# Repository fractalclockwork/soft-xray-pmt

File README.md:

# soft-xray-pmt — Soft X-ray PMT (XP3312/SQ), stage 1

This repo is the **first stage** of a soft X-ray detector: power and sense bring-up for a surplus Photonis **XP3312/SQ** (SN 294056) on a wooden harness with its stock Philips medical I/O filter board (dual-row header + coax + local R/C). The board is a **filter/breakout**, not a full dynode divider — the Type A HV string and anode path are designed here before later detector integration. **No HV applied yet.**

*Bring-up harness: tube cradled on plywood, stock circular filter PCB, divider protoboard, banana HV + BNC anode.*

*Photocathode end of the tube in the harness cradles.*

## Prior — verified pin map (continuity 2026-11-01)

Unpowered DMM checks locked the tube↔header map and corrected the filter cluster. **PASS.** This is the prior gate for HV bring-up — not an energize stage.

| Item | Path |
|---|---|
| **Verified netlist** | [`docs/probable-netlist.md`](docs/probable-netlist.md) |
| Pin reconciliation | [`docs/pin-reconciliation.md`](docs/pin-reconciliation.md) |
| Continuity checklist | [`docs/continuity-checklist.md`](docs/continuity-checklist.md) |
| KiCad project | [`hardware/pmt-interface/`](hardware/pmt-interface/) |
| Schematic (page 1 filter) | [`hardware/pmt-interface/pmt-interface.kicad_sch`](hardware/pmt-interface/pmt-interface.kicad_sch) |
| Schematic (page 2 bringup) | [`hardware/pmt-interface/bringup-supply.kicad_sch`](hardware/pmt-interface/bringup-supply.kicad_sch) |
| Filter PCB (2-layer analogue) | [`hardware/pmt-interface/pmt-interface.kicad_pcb`](hardware/pmt-interface/pmt-interface.kicad_pcb) |
| Bring-up supply PCB | [`hardware/pmt-interface/bringup-supply.kicad_pcb`](hardware/pmt-interface/bringup-supply.kicad_pcb) |
| Filter PCB preview | [`docs/pmt-interface-pcb.pdf`](docs/pmt-interface-pcb.pdf) |
| Circular pin map | [`docs/tube-pin-map.md`](docs/tube-pin-map.md) |
| PDF preview | [`docs/pmt-interface-draft.pdf`](docs/pmt-interface-draft.pdf) |
| Photo BOM / traces | [`docs/photo-bom.md`](docs/photo-bom.md), [`docs/photo-trace-map.md`](docs/photo-trace-map.md) |
| Datasheets | [`docs/sources.md`](docs/sources.md), [`docs/datasheets/`](docs/datasheets/) |
| Board photos | [`docs/img/`](docs/img/) |
| Bring-up harness photos | [`docs/img/bringup/`](docs/img/bringup/) |

## HV bring-up (multi-stage)

Gated ladder: design/build divider + anode measure **before** any HV; dark ramp with encoded voltage ceilings; scope anode before Pico. **No HV applied yet.**

| Item | Path |
|---|---|
| **Bring-up index + status** | [`docs/bringup/README.md`](docs/bringup/README.md) |
| Voltage / current ceilings | [`docs/bringup/ceilings.md`](docs/bringup/ceilings.md) |
| **Bring-up BOM** (divider + anode + DNP) | [`docs/bringup/bom-divider.md`](docs/bringup/bom-divider.md) |
| Gate 0 design | [`docs/bringup/gate-0-design.md`](docs/bringup/gate-0-design.md) (**PASS**) |
| Gate 0b sch verify | [`docs/bringup/gate-0-sch-verify.md`](docs/bringup/gate-0-sch-verify.md) (**PASS**) |
| Gate 0c SPICE | [`docs/bringup/gate-0-spice.md`](docs/bringup/gate-0-spice.md) — KiCad (**PASS**) |
| Gate PCB bringup-supply | [`docs/bringup/gate-pcb-bringup.md`](docs/bringup/gate-pcb-bringup.md) (**PASS** 2026-11-02) |
| Next | Gate A stuff per [`bom-divider.md`](docs/bringup/bom-divider.md) → B → C → Stages 1–8 |

Ceilings (first pass): Stage 1 **100 V** → Stage 2 **400 V** → Stage 3 **800 V** → Stage 4 **1000 V** dark; abs max **1500 V**.

Gated sch→PCB: skill `kicad-gated-sch-pcb`; instance [`docs/bringup/design-process.md`](docs/bringup/design-process.md), commands [`hardware/pmt-interface/AGENTS.md`](hardware/pmt-interface/AGENTS.md).  
Schematic routing: [`.cursor/skills/kicad-schematic-routing/SKILL.md`](.cursor/skills/kicad-schematic-routing/SKILL.md).

```bash
python3 hardware/pmt-interface/gen_bringup_sch.py --validate   # tracked sch; no overwrite
python3 hardware/pmt-interface/gen_fp.py
python3 hardware/pmt-interface/gen_sch.py --validate          # page 1; does not rewrite bringup sch
python3 hardware/pmt-interface/gen_pcb.py                     # filter analogue (outside Gate PCB)
```

## Tube identity

- Photonis XP3312/SQ — Made in France
- Date 29-Sep-04, batch 04229, SN 294056
- PH 36 pC, PHR 8.7%

## Verified board map (summary)

Tube view: **bottom looking up**, `sp` south, pins **1…19 clockwise**.

J1 is a **DIP-14–style wide IC socket** (7.62 mm / 300 mil row spacing, wrap numbering — **not** IDC ribbon Odd/Even):

```text
  1 -------- 14
  2 -------- 13
  ...
  7 --------  8
```

| Electrode | Tube | Board |
|---|---|---|
| D1…D8 | 1,3,4,7,8,9,10,11 | J1 **8,9,6,5,4,12,3,2** |
| K | 16 | C1 `472Z` 2 kV to GND; R1 `1001` 1 kΩ → **J1.7** |
| A | 12 | coax center; R2 `115` ~1.1 MΩ → GND |
| GND | — | **J1.14** + coax shell |
| Filter | — | **D8** and **J1.13** each via tan MLCC to mid → R3 `100` 10 Ω → GND |

J1.1 / 10 / 11: photo-consistent NC (pads, no fan-out); DMM still required (11 least clear).

## License

SPDX-License-Identifier: `CERN-OHL-S-2.0`

Hardware sources and accompanying project materials are under the [CERN Open Hardware Licence Version 2 - Strongly Reciprocal](LICENSE). See also [`NOTICE`](NOTICE).

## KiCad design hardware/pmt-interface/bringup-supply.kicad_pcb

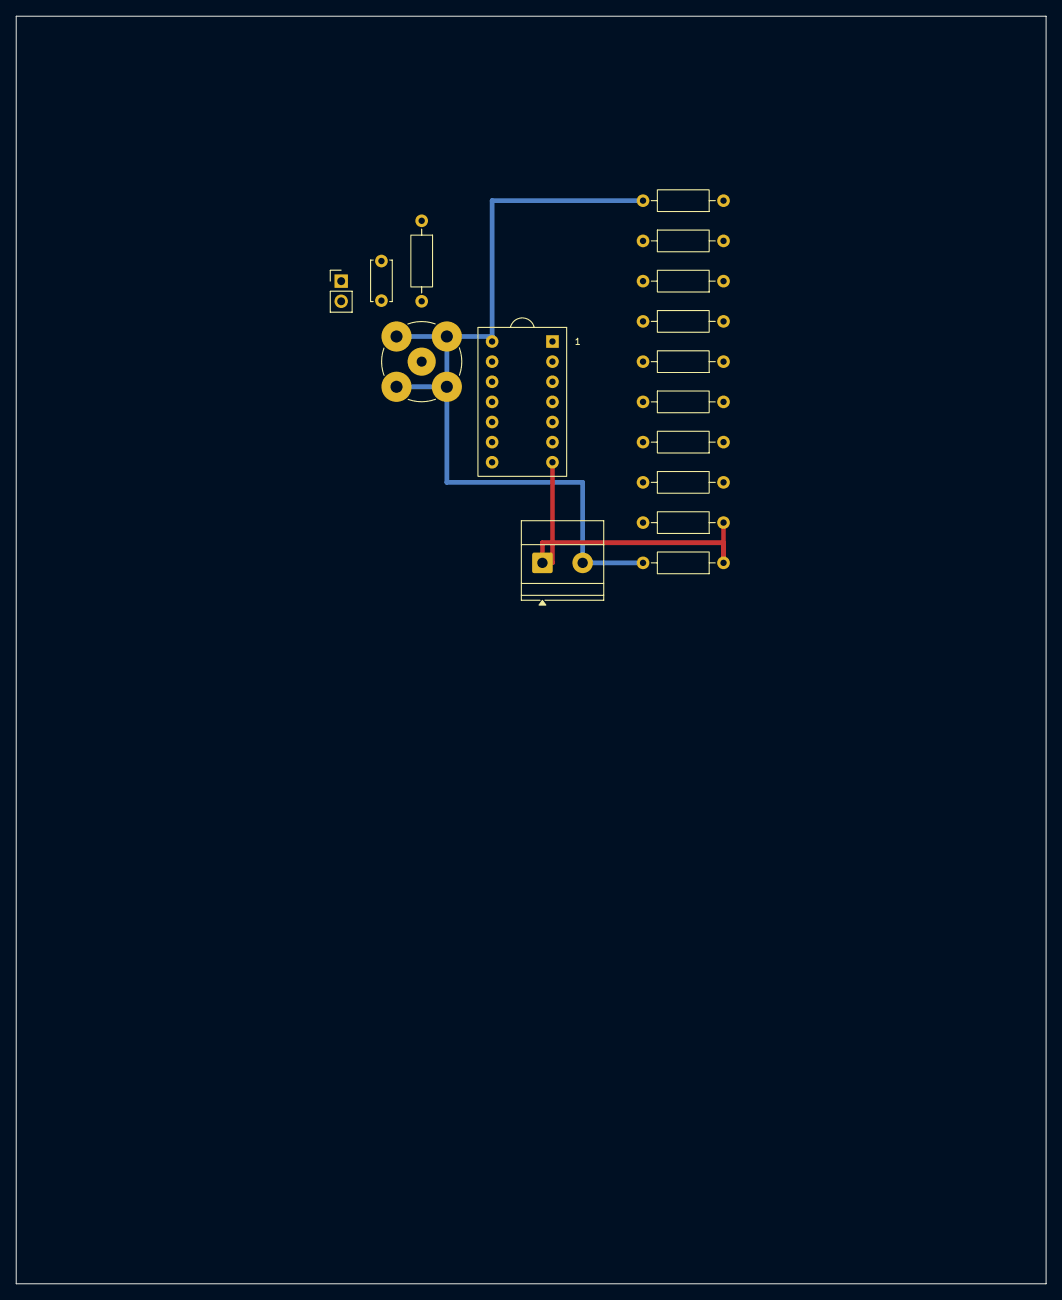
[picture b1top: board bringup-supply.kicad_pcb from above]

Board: 10 copper layers, 130.0 x 160.0 mm, 16 parts (0 on the bottom side), 12 nets.

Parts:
C4: 1nF; C_Disc_D5.0mm_W2.5mm_P5.00mm
J3: HV_IN; TerminalBlock_Phoenix_MKDS-1,5-2-5.08_1x02_P5.08mm_Horizont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
J4: MATE_J1; HDR_2x7_IC_Socket
J5: BNC_SCOPE; BNC_TEConnectivity_1478204_Vertical
JMP_DC: DC_COUPLE; PinHeader_1x02_P2.54mm_Vertical
R10: 4.4M; R_Axial_DIN0207_L6.3mm_D2.5mm_P10.16mm_Horizontal
R11, R12, R13: 3.3M; R_Axial_DIN0207_L6.3mm_D2.5mm_P10.16mm_Horizontal
R14, R15, R16, R17: 2.2M; R_Axial_DIN0207_L6.3mm_D2.5mm_P10.16mm_Horizontal
R18: 1.1M; R_Axial_DIN0207_L6.3mm_D2.5mm_P10.16mm_Horizontal
R19: 47R; R_Axial_DIN0207_L6.3mm_D2.5mm_P10.16mm_Horizontal
Rbleed: 22M; R_Axial_DIN0207_L6.3mm_D2.5mm_P10.16mm_Horizontal

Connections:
A: C4.1, JMP_DC.1, R19.1
D1: J4.8, R10.2, R11.1
D2: J4.9, R11.2, R12.1
D3: J4.6, R12.2, R13.1
D4: J4.5, R13.2, R14.1
D5: J4.4, R14.2, R15.1
D6: J4.12, R15.2, R16.1
D7: J4.3, R16.2, R17.1
D8: J4.2, R17.2, R18.1
GND: J3.2, J4.14, J5.2, R18.2, Rbleed.2
K: J3.1, J4.7, R10.1, Rbleed.1
SCOPE: C4.2, J5.1, JMP_DC.2, R19.2

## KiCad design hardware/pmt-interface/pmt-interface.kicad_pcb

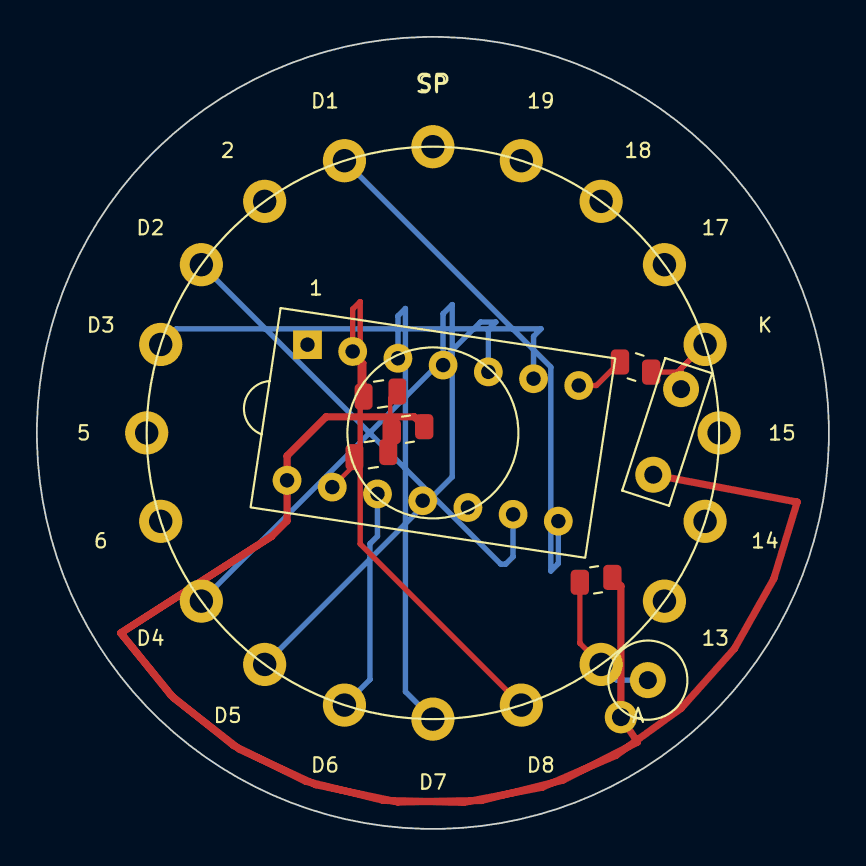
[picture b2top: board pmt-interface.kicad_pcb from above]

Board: 2 copper layers, 44.0 x 44.0 mm, 9 parts (1 on the bottom side), 14 nets.

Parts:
C1: 4.7nF 2kV; C_Disc_D7.5mm_W2.5mm_P5.00mm
C2: MLCC J1.13; C_0805_2012Metric
C3: MLCC D8; C_0805_2012Metric
J1: HDR_2x7_IC_Socket
J2: COAX; COAX_Edge
R1: 1k; R_0805_2012Metric
R2: 1.1M; R_0805_2012Metric
R3: 10R; R_0805_2012Metric
U1: XP3312/SQ; XP3312_FlyingLead

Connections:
A: J2.1, R2.1, U1.12
BYPASS_MID: C2.2, C3.2, R3.1
D1: J1.8, U1.1
D2: J1.9, U1.3
D3: J1.6, U1.4
D4: J1.5, U1.7
D5: J1.4, U1.8
D6: J1.12, U1.9
D7: J1.3, U1.10
D8: C3.1, J1.2, U1.11
GND: C1.2, J1.14, J2.2, R2.2, R3.2
J1.13: C2.1, J1.13
K: C1.1, R1.1, U1.16
R1_J1: J1.7, R1.2

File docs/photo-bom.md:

# Photo BOM — stock XP3312/SQ I/O filter board

Confidence: `FROM_PHOTO` unless noted. Values preferred over pencil notes when they conflict.

## Tube

| Field | Value | Source |
|---|---|---|
| Maker | PHOTONIS imaging sensors | IMG_6985 / 6998 |
| Type | XP3312/SQ | label |
| Date | 29-Sep-04 | label |
| Batch | 04229 | label |
| SN | 294056 | label |
| PH | 36 pC | label |
| PHR | 8.7% | label |
| Origin | Made in France | label |
| Side code | 331117031963 | label |

## Passive components on filter PCB

| Ref (draft) | Marking | Interpreted value | Role (hypothesis) | Photos |
|---|---|---|---|---|
| R1 / R_K | `1001` | **1 kΩ** | Cathode path series to header pin 7 | 6989, 7006 |
| R2 / R_A | `115` | **1.1 MΩ** | Anode load to GND (notes said 1 M) | 7005 |
| R3 / R_F | `100` | **10 Ω** | Mid-node → GND (between two filter MLCCs) | 7005 |
| C1 / C_HV | `472Z` `2KV` | **4.7 nF, Z tol, 2 kV** | Cathode bypass to GND | **7006** |
| C2 / C_F1 | unmarked tan MLCC | TBD (measure / mark) | **J1.13** ↔ filter mid (continuity) | 6993, 7005 |
| C3 / C_F2 | unmarked tan MLCC | TBD | **D8** ↔ filter mid (continuity) | 6993, 7005 |

## Connectors

| Ref | Description | Notes |
|---|---|---|
| J1 | **Wide IC / DIP-14 style socket** (≈7.62 mm row spacing, two rows of 7) | **Wrap numbering** (1–7 \| 14–8) like Prutchi XP2422 Fig. 3 / DIP-14; **not** IDC ribbon Odd/Even or 2.54 mm dual-row header body |
| J2 | Gold coax (SMA/SMB-style) | Center = anode signal; shell = GND |

## Mechanical

- Circular green PCB on three black standoffs at tube base
- Flying leads from tube soldered to perimeter pads
- Board is **filter + breakout**, not a full dynode divider (matches Prutchi / community)
